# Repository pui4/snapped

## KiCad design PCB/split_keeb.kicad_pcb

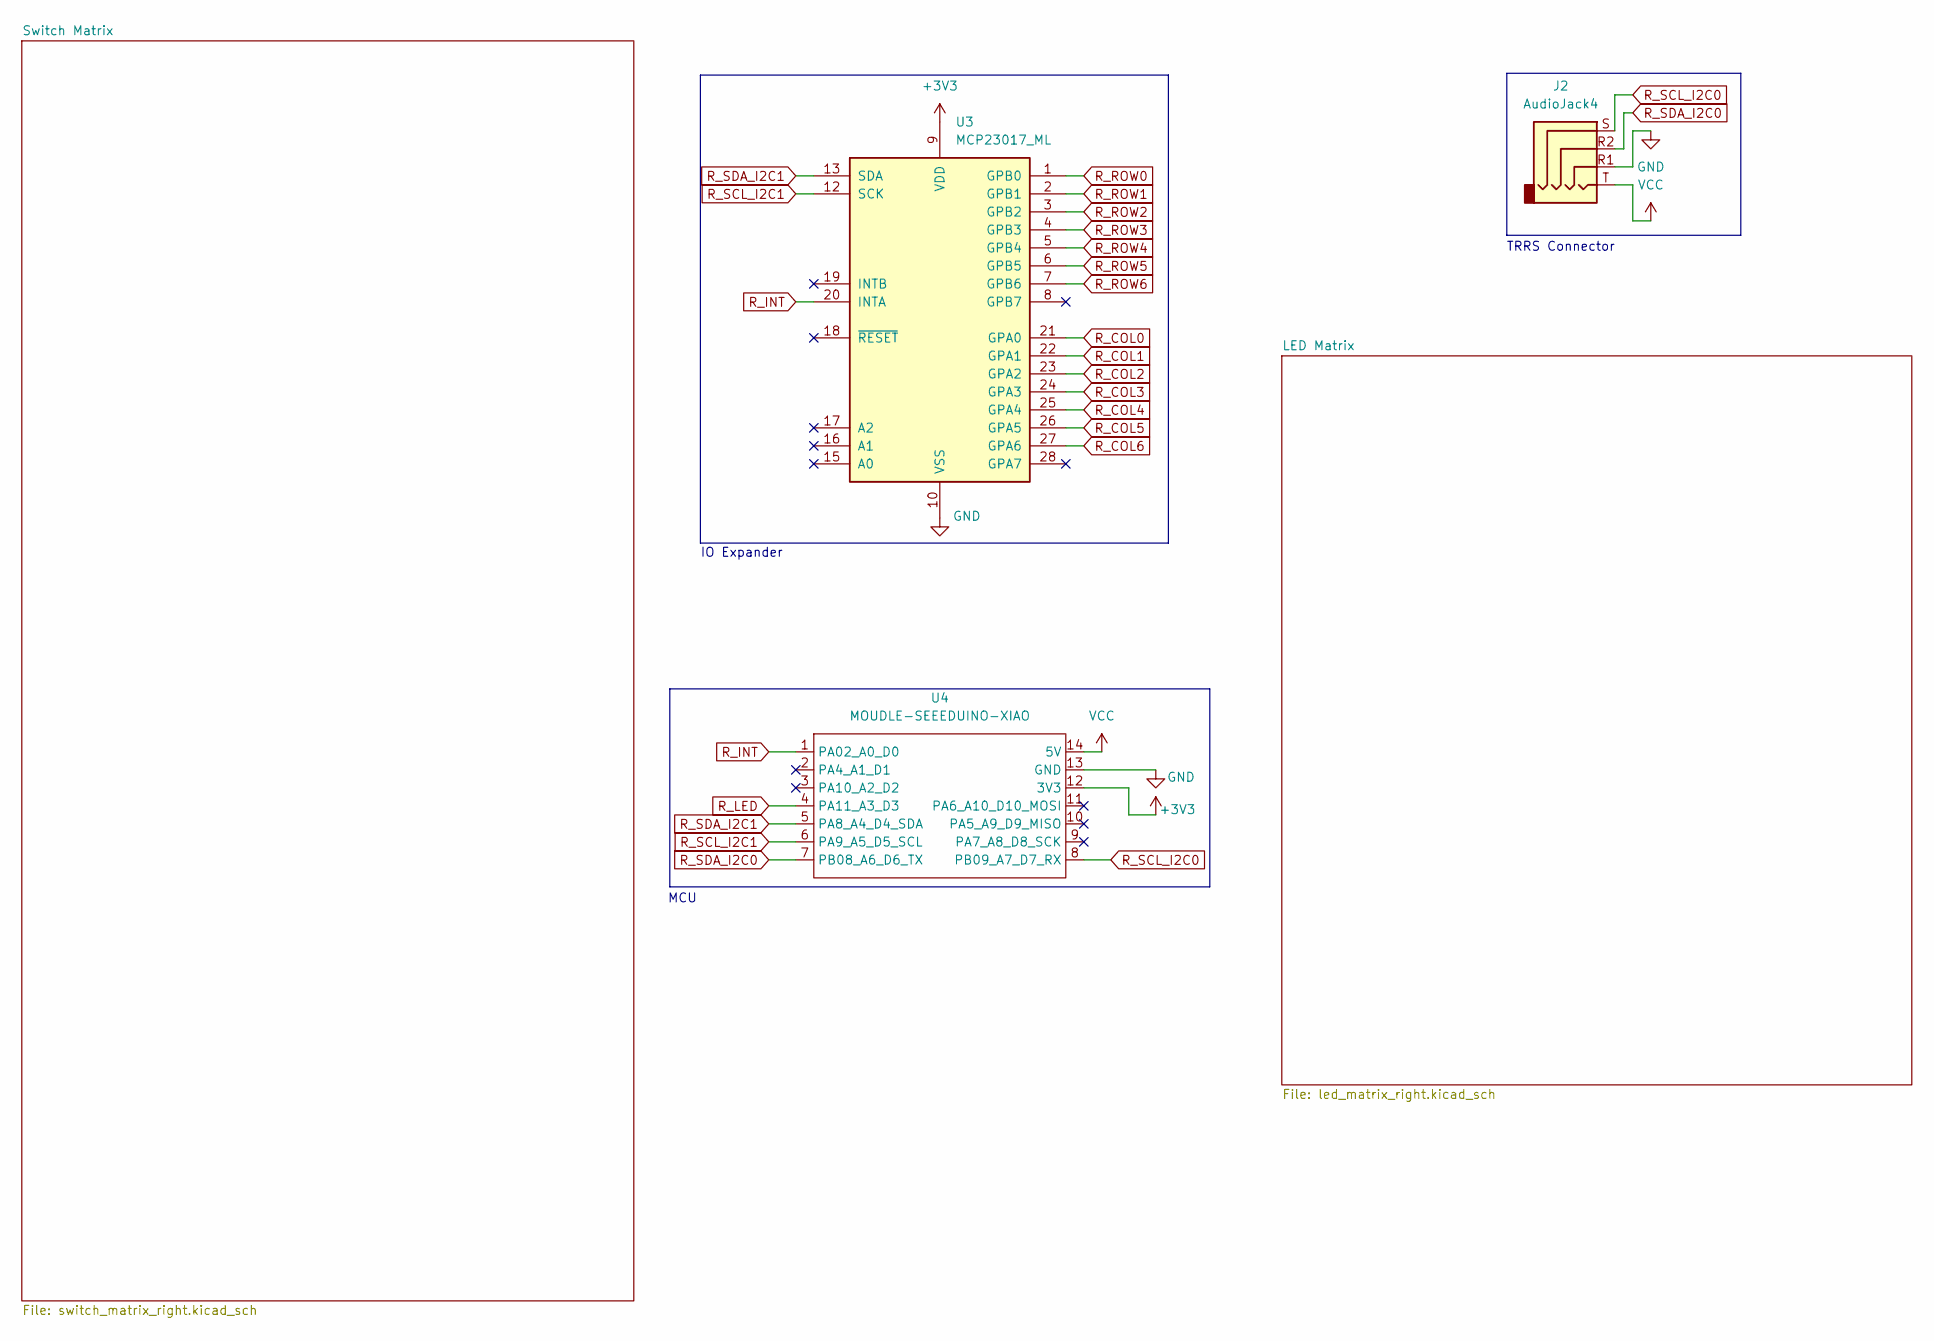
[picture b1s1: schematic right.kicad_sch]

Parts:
J2: AudioJack4; Jack_3.5mm_PJ320D_Horizontal
U3: MCP23017_ML; DIP-28_W7.62mm
U4: MOUDLE-SEEEDUINO-XIAO; XIAO-Generic-Hybrid-14P-2.54-21X17.8MM

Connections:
+3V3: U3.9 (VDD), U4.12 (3V3); also elsewhere on the board
GND: J2.R1, U3.10 (VSS), U4.13 (GND); also elsewhere on the board
R_COL0: U3.21 (GPA0); also elsewhere on the board
R_COL1: U3.22 (GPA1); also elsewhere on the board
R_COL2: U3.23 (GPA2); also elsewhere on the board
R_COL3: U3.24 (GPA3); also elsewhere on the board
R_COL4: U3.25 (GPA4); also elsewhere on the board
R_COL5: U3.26 (GPA5); also elsewhere on the board
R_COL6: U3.27 (GPA6); also elsewhere on the board
R_INT: U3.20 (INTA), U4.1 (PA02_A0_D0)
R_LED: U4.4 (PA11_A3_D3); also elsewhere on the board
R_ROW0: U3.1 (GPB0); also elsewhere on the board
R_ROW1: U3.2 (GPB1); also elsewhere on the board
R_ROW2: U3.3 (GPB2); also elsewhere on the board
R_ROW3: U3.4 (GPB3); also elsewhere on the board
R_ROW4: U3.5 (GPB4); also elsewhere on the board
R_ROW5: U3.6 (GPB5); also elsewhere on the board
R_ROW6: U3.7 (GPB6); also elsewhere on the board
R_SCL_I2C0: J2.S, U4.8 (PB09_A7_D7_RX)
R_SCL_I2C1: U3.12 (SCK), U4.6 (PA9_A5_D5_SCL)
R_SDA_I2C0: J2.R2, U4.7 (PB08_A6_D6_TX)
R_SDA_I2C1: U3.13 (SDA), U4.5 (PA8_A4_D4_SDA)
VCC: J2.T, U4.14 (5V); also elsewhere on the board

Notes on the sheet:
IO Expander
TRRS Connector
MCU

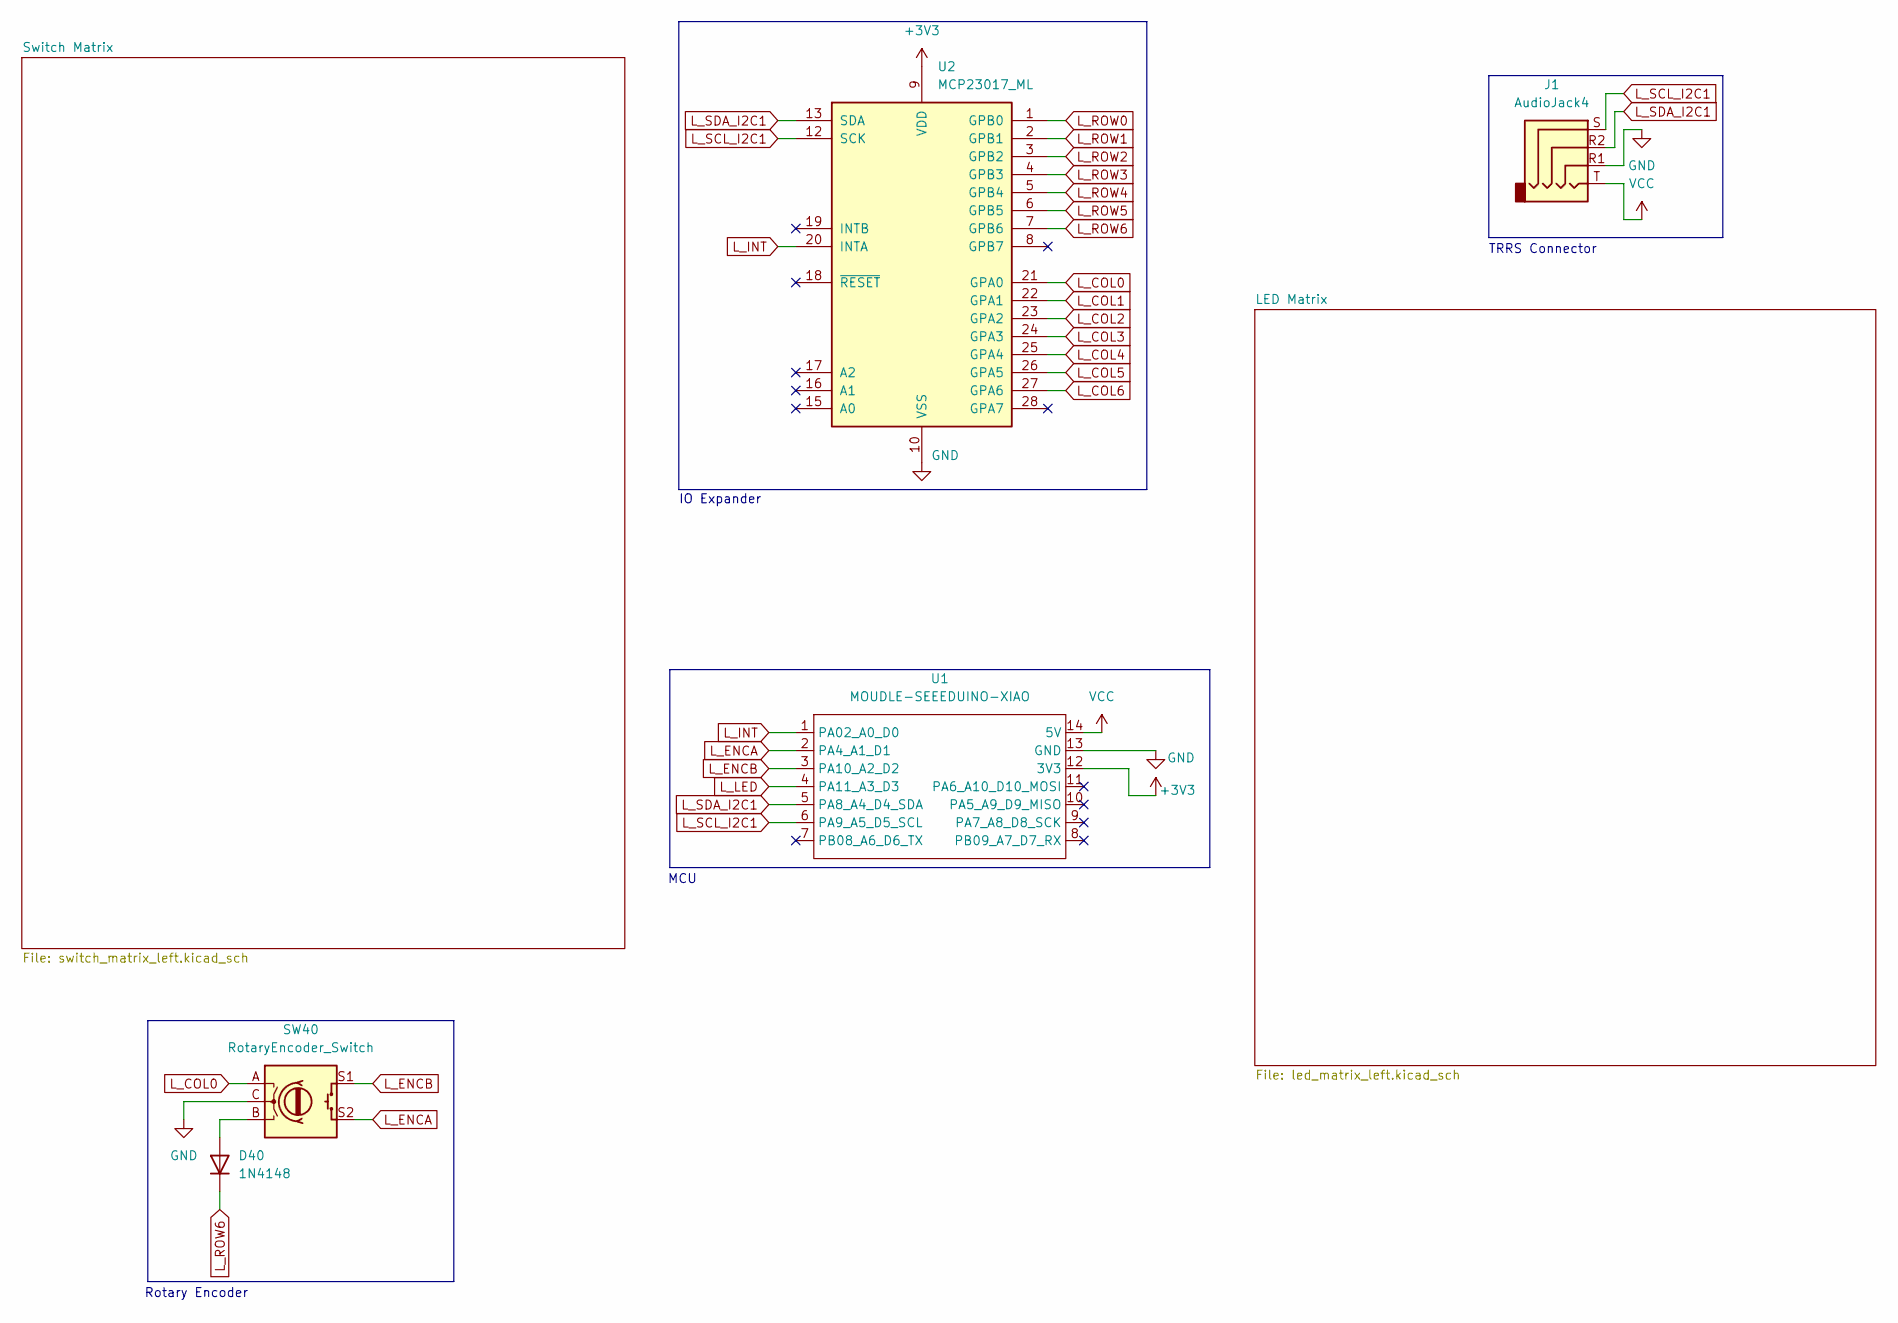
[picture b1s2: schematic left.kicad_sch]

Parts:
D40: 1N4148; D_DO-35_SOD27_P7.62mm_Horizontal
J1: AudioJack4; Jack_3.5mm_PJ320D_Horizontal
SW40: RotaryEncoder_Switch; RotaryEncoder_Alps_EC11E-Switch_Vertical_H20mm
U1: MOUDLE-SEEEDUINO-XIAO; XIAO-Generic-Hybrid-14P-2.54-21X17.8MM
U2: MCP23017_ML; DIP-28_W7.62mm

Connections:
+3V3: U1.12 (3V3), U2.9 (VDD); also elsewhere on the board
GND: J1.R1, SW40.C, U1.13 (GND), U2.10 (VSS); also elsewhere on the board
L_COL0: SW40.A, U2.21 (GPA0); also elsewhere on the board
L_COL1: U2.22 (GPA1); also elsewhere on the board
L_COL2: U2.23 (GPA2); also elsewhere on the board
L_COL3: U2.24 (GPA3); also elsewhere on the board
L_COL4: U2.25 (GPA4); also elsewhere on the board
L_COL5: U2.26 (GPA5); also elsewhere on the board
L_COL6: U2.27 (GPA6); also elsewhere on the board
L_ENCA: SW40.S2, U1.2 (PA4_A1_D1)
L_ENCB: SW40.S1, U1.3 (PA10_A2_D2)
L_INT: U1.1 (PA02_A0_D0), U2.20 (INTA)
L_LED: U1.4 (PA11_A3_D3); also elsewhere on the board
L_ROW0: U2.1 (GPB0); also elsewhere on the board
L_ROW1: U2.2 (GPB1); also elsewhere on the board
L_ROW2: U2.3 (GPB2); also elsewhere on the board
L_ROW3: U2.4 (GPB3); also elsewhere on the board
L_ROW4: U2.5 (GPB4); also elsewhere on the board
L_ROW5: U2.6 (GPB5); also elsewhere on the board
L_ROW6: D40.1 (K), U2.7 (GPB6); also elsewhere on the board
L_SCL_I2C1: J1.S, U1.6 (PA9_A5_D5_SCL), U2.12 (SCK)
L_SDA_I2C1: J1.R2, U1.5 (PA8_A4_D4_SDA), U2.13 (SDA)
unnamed: D40.2 (A), SW40.B
VCC: J1.T, U1.14 (5V); also elsewhere on the board

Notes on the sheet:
TRRS Connector
MCU
IO Expander
Rotary Encoder

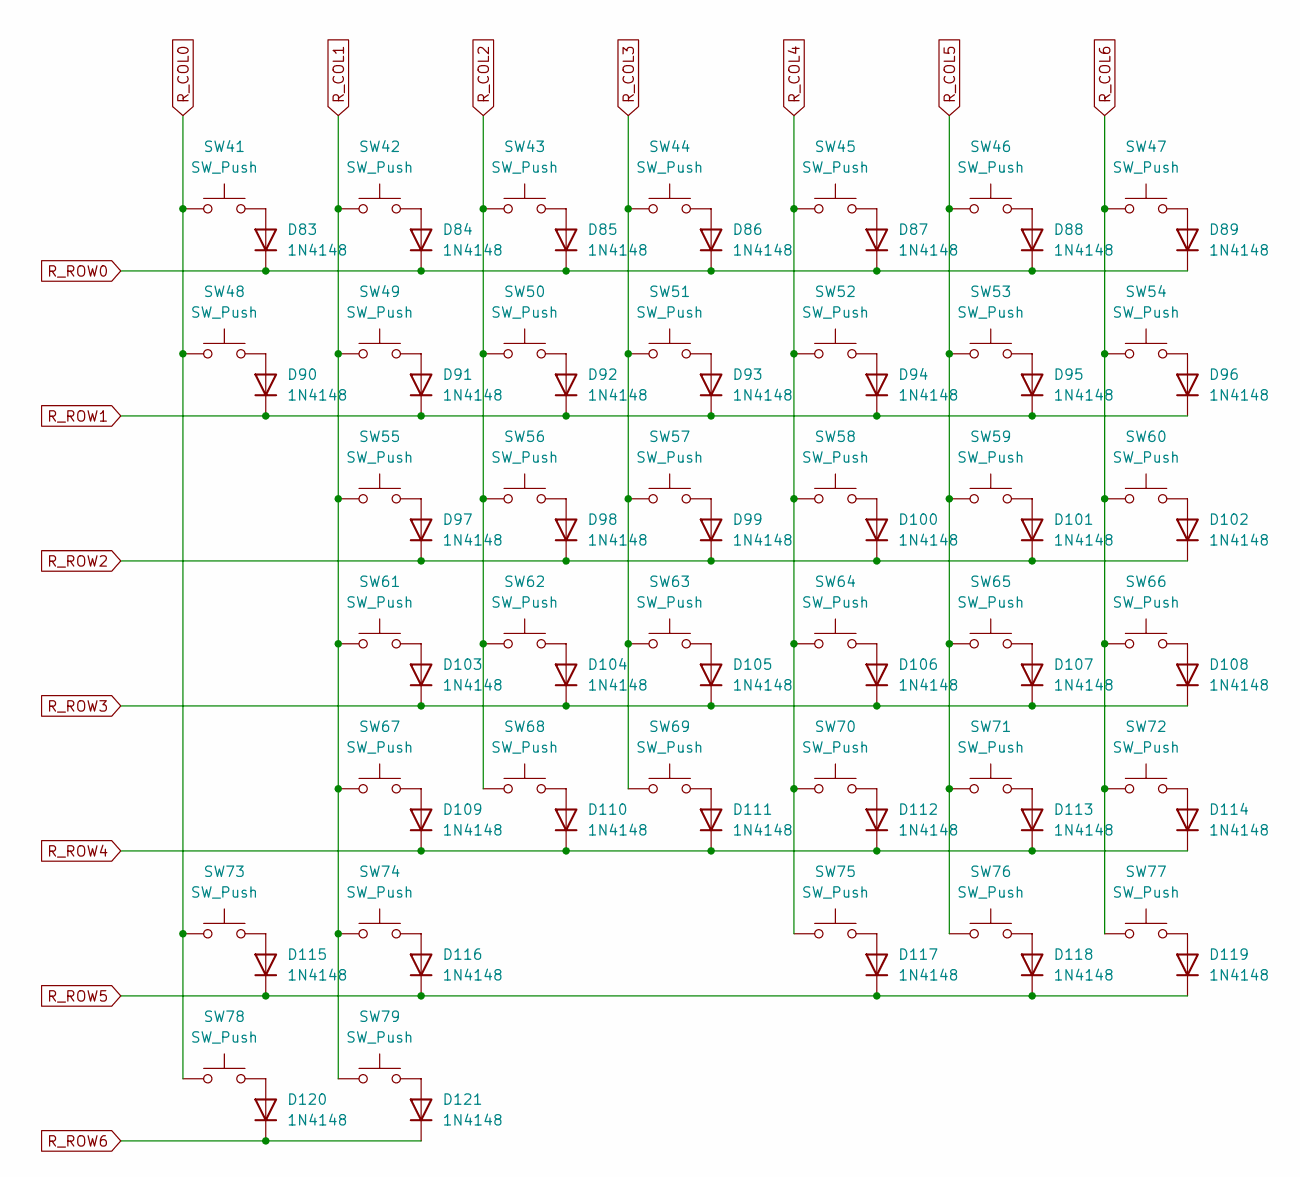
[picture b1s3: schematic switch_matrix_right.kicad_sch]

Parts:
D83, D84, D85, D86, D87, D88, D89, D90, D91, D92, D93, D94, D95, D96, D97, D98, D99, D100, D101, D102, D103, D104, D105, D106, D107, D108, D109, D110, D111, D112, D113, D114, D115, D116, D117, D118, D119, D120, D121: 1N4148; D_DO-35_SOD27_P7.62mm_Horizontal
SW41, SW42, SW43, SW44, SW45, SW46, SW47, SW48, SW49, SW50, SW51, SW52, SW53, SW54, SW55, SW56, SW57, SW58, SW59, SW61, SW62, SW63, SW64, SW65, SW67, SW68, SW69, SW70, SW71, SW74, SW75, SW76, SW79: SW_Push; SW_KS33_HS_KS-2P02B01-02_HS_1u
SW60, SW66, SW72, SW77: SW_Push; SW_KS33_HS_KS-2P02B01-02_1.25u
SW73, SW78: SW_Push; SW_KS33_HS_KS-2P02B01-02_1.75u

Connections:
unnamed: D83.2 (A), SW41.2
unnamed: D84.2 (A), SW42.2
unnamed: D85.2 (A), SW43.2
unnamed: D86.2 (A), SW44.2
unnamed: D87.2 (A), SW45.2
unnamed: D88.2 (A), SW46.2
unnamed: D89.2 (A), SW47.2
unnamed: D90.2 (A), SW48.2
unnamed: D91.2 (A), SW49.2
unnamed: D92.2 (A), SW50.2
unnamed: D93.2 (A), SW51.2
unnamed: D94.2 (A), SW52.2
unnamed: D95.2 (A), SW53.2
unnamed: D96.2 (A), SW54.2
unnamed: D97.2 (A), SW55.2
unnamed: D98.2 (A), SW56.2
unnamed: D99.2 (A), SW57.2
unnamed: D100.2 (A), SW58.2
unnamed: D101.2 (A), SW59.2
unnamed: D102.2 (A), SW60.2
unnamed: D103.2 (A), SW61.2
unnamed: D104.2 (A), SW62.2
unnamed: D105.2 (A), SW63.2
unnamed: D106.2 (A), SW64.2
unnamed: D107.2 (A), SW65.2
unnamed: D108.2 (A), SW66.2
unnamed: D109.2 (A), SW67.2
unnamed: D110.2 (A), SW68.2
unnamed: D111.2 (A), SW69.2
unnamed: D112.2 (A), SW70.2
unnamed: D113.2 (A), SW71.2
unnamed: D114.2 (A), SW72.2
unnamed: D115.2 (A), SW73.2
unnamed: D116.2 (A), SW74.2
unnamed: D117.2 (A), SW75.2
unnamed: D118.2 (A), SW76.2
unnamed: D119.2 (A), SW77.2
unnamed: D120.2 (A), SW78.2
unnamed: D121.2 (A), SW79.2
R_COL0: SW41.1, SW48.1, SW73.1, SW78.1; also elsewhere on the board
R_COL1: SW42.1, SW49.1, SW55.1, SW61.1, SW67.1, SW74.1, SW79.1; also elsewhere on the board
R_COL2: SW43.1, SW50.1, SW56.1, SW62.1, SW68.1; also elsewhere on the board
R_COL3: SW44.1, SW51.1, SW57.1, SW63.1, SW69.1; also elsewhere on the board
R_COL4: SW45.1, SW52.1, SW58.1, SW64.1, SW70.1, SW75.1; also elsewhere on the board
R_COL5: SW46.1, SW53.1, SW59.1, SW65.1, SW71.1, SW76.1; also elsewhere on the board
R_COL6: SW47.1, SW54.1, SW60.1, SW66.1, SW72.1, SW77.1; also elsewhere on the board
R_ROW0: D83.1 (K), D84.1 (K), D85.1 (K), D86.1 (K), D87.1 (K), D88.1 (K), D89.1 (K); also elsewhere on the board
R_ROW1: D90.1 (K), D91.1 (K), D92.1 (K), D93.1 (K), D94.1 (K), D95.1 (K), D96.1 (K); also elsewhere on the board
R_ROW2: D97.1 (K), D98.1 (K), D99.1 (K), D100.1 (K), D101.1 (K), D102.1 (K); also elsewhere on the board
R_ROW3: D103.1 (K), D104.1 (K), D105.1 (K), D106.1 (K), D107.1 (K), D108.1 (K); also elsewhere on the board
R_ROW4: D109.1 (K), D110.1 (K), D111.1 (K), D112.1 (K), D113.1 (K), D114.1 (K); also elsewhere on the board
R_ROW5: D115.1 (K), D116.1 (K), D117.1 (K), D118.1 (K), D119.1 (K); also elsewhere on the board
R_ROW6: D120.1 (K), D121.1 (K); also elsewhere on the board

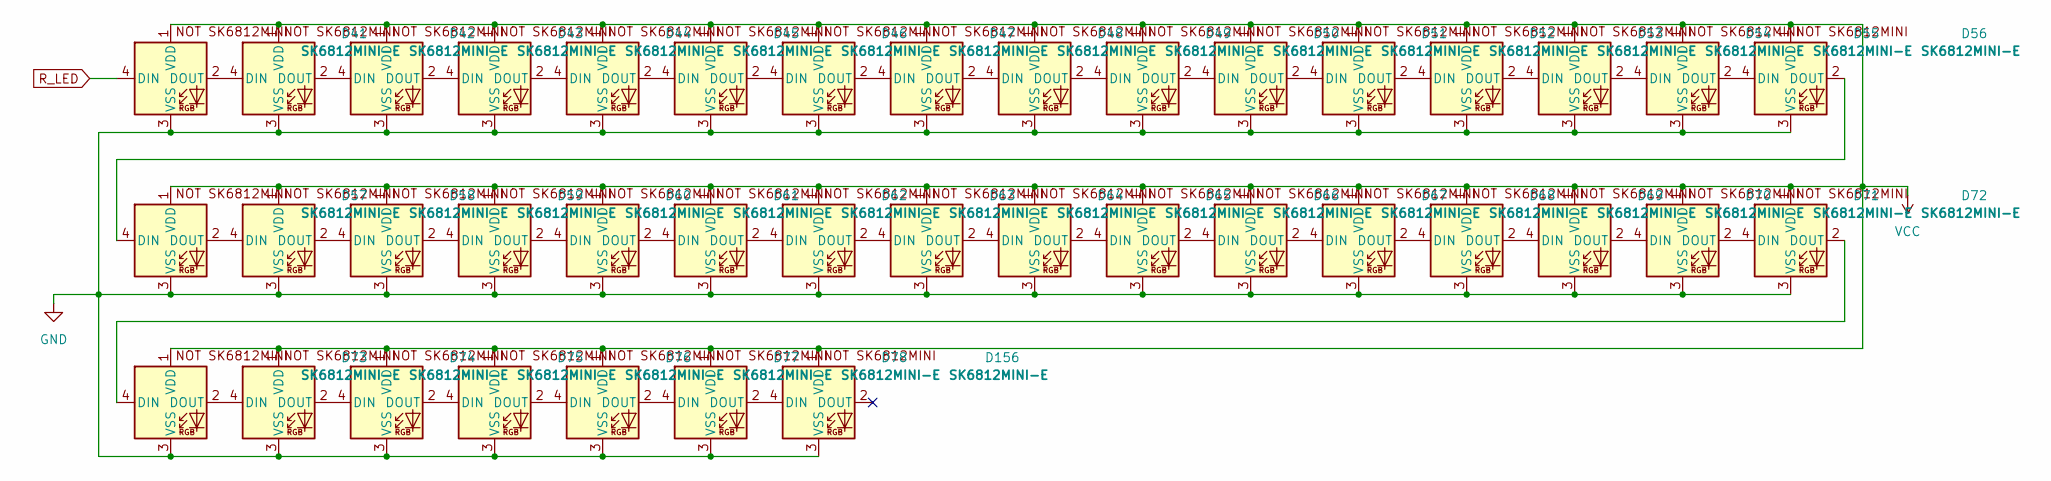
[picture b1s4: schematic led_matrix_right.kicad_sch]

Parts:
D41, D42, D43, D44, D45, D46, D47, D48, D49, D50, D51, D52, D53, D54, D55, D56, D57, D58, D59, D60, D61, D62, D63, D64, D65, D66, D67, D68, D69, D70, D71, D72, D73, D74, D75, D76, D77, D78, D156: SK6812MINI-E; SK6812MINI-E_fixed

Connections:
GND: D41.3 (VSS), D42.3 (VSS), D43.3 (VSS), D44.3 (VSS), D45.3 (VSS), D46.3 (VSS), D47.3 (VSS), D48.3 (VSS), D49.3 (VSS), D50.3 (VSS), D51.3 (VSS), D52.3 (VSS), D53.3 (VSS), D54.3 (VSS), D55.3 (VSS), D56.3 (VSS), D57.3 (VSS), D58.3 (VSS), D59.3 (VSS), D60.3 (VSS), D61.3 (VSS), D62.3 (VSS), D63.3 (VSS), D64.3 (VSS), D65.3 (VSS), D66.3 (VSS), D67.3 (VSS), D68.3 (VSS), D69.3 (VSS), D70.3 (VSS), D71.3 (VSS), D72.3 (VSS), D73.3 (VSS), D74.3 (VSS), D75.3 (VSS), D76.3 (VSS), D77.3 (VSS), D78.3 (VSS), D156.3 (VSS); also elsewhere on the board
unnamed: D41.2 (DOUT), D42.4 (DIN)
unnamed: D42.2 (DOUT), D43.4 (DIN)
unnamed: D43.2 (DOUT), D44.4 (DIN)
unnamed: D44.2 (DOUT), D45.4 (DIN)
unnamed: D45.2 (DOUT), D46.4 (DIN)
unnamed: D46.2 (DOUT), D47.4 (DIN)
unnamed: D47.2 (DOUT), D48.4 (DIN)
unnamed: D48.2 (DOUT), D49.4 (DIN)
unnamed: D49.2 (DOUT), D50.4 (DIN)
unnamed: D50.2 (DOUT), D51.4 (DIN)
unnamed: D51.2 (DOUT), D52.4 (DIN)
unnamed: D52.2 (DOUT), D53.4 (DIN)
unnamed: D53.2 (DOUT), D54.4 (DIN)
unnamed: D54.2 (DOUT), D55.4 (DIN)
unnamed: D55.2 (DOUT), D56.4 (DIN)
unnamed: D56.2 (DOUT), D57.4 (DIN)
unnamed: D57.2 (DOUT), D58.4 (DIN)
unnamed: D58.2 (DOUT), D59.4 (DIN)
unnamed: D59.2 (DOUT), D60.4 (DIN)
unnamed: D60.2 (DOUT), D61.4 (DIN)
unnamed: D61.2 (DOUT), D62.4 (DIN)
unnamed: D62.2 (DOUT), D63.4 (DIN)
unnamed: D63.2 (DOUT), D64.4 (DIN)
unnamed: D64.2 (DOUT), D65.4 (DIN)
unnamed: D65.2 (DOUT), D66.4 (DIN)
unnamed: D66.2 (DOUT), D67.4 (DIN)
unnamed: D67.2 (DOUT), D68.4 (DIN)
unnamed: D68.2 (DOUT), D69.4 (DIN)
unnamed: D69.2 (DOUT), D70.4 (DIN)
unnamed: D70.2 (DOUT), D71.4 (DIN)
unnamed: D71.2 (DOUT), D72.4 (DIN)
unnamed: D72.2 (DOUT), D73.4 (DIN)
unnamed: D73.2 (DOUT), D74.4 (DIN)
unnamed: D74.2 (DOUT), D75.4 (DIN)
unnamed: D75.2 (DOUT), D76.4 (DIN)
unnamed: D76.2 (DOUT), D77.4 (DIN)
unnamed: D77.2 (DOUT), D78.4 (DIN)
unnamed: D78.2 (DOUT), D156.4 (DIN)
R_LED: D41.4 (DIN); also elsewhere on the board
VCC: D41.1 (VDD), D42.1 (VDD), D43.1 (VDD), D44.1 (VDD), D45.1 (VDD), D46.1 (VDD), D47.1 (VDD), D48.1 (VDD), D49.1 (VDD), D50.1 (VDD), D51.1 (VDD), D52.1 (VDD), D53.1 (VDD), D54.1 (VDD), D55.1 (VDD), D56.1 (VDD), D57.1 (VDD), D58.1 (VDD), D59.1 (VDD), D60.1 (VDD), D61.1 (VDD), D62.1 (VDD), D63.1 (VDD), D64.1 (VDD), D65.1 (VDD), D66.1 (VDD), D67.1 (VDD), D68.1 (VDD), D69.1 (VDD), D70.1 (VDD), D71.1 (VDD), D72.1 (VDD), D73.1 (VDD), D74.1 (VDD), D75.1 (VDD), D76.1 (VDD), D77.1 (VDD), D78.1 (VDD), D156.1 (VDD); also elsewhere on the board

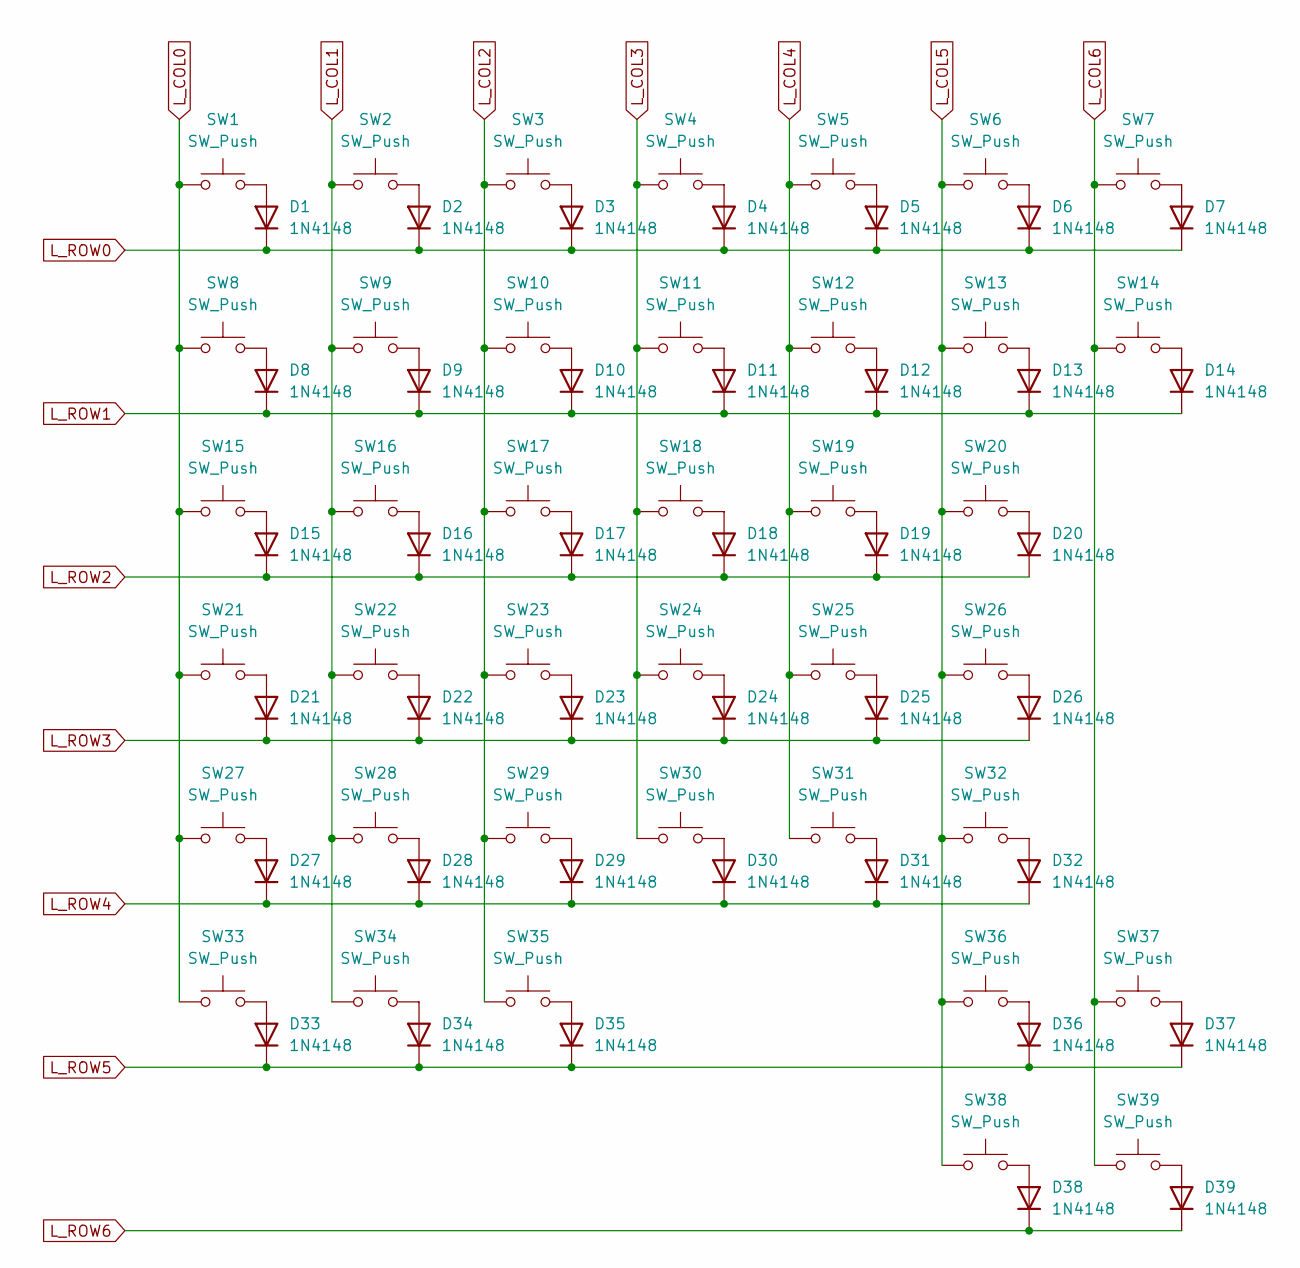
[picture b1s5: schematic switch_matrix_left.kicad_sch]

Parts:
D1, D2, D3, D4, D5, D6, D7, D8, D9, D10, D11, D12, D13, D14, D15, D16, D17, D18, D19, D20, D21, D22, D23, D24, D25, D26, D27, D28, D29, D30, D31, D32, D33, D34, D35, D36, D37, D38, D39: 1N4148; D_DO-35_SOD27_P7.62mm_Horizontal
SW1, SW2, SW3, SW4, SW5, SW6, SW7, SW8, SW9, SW10, SW11, SW12, SW13, SW14, SW16, SW17, SW18, SW19, SW20, SW22, SW23, SW24, SW25, SW26, SW28, SW29, SW30, SW31, SW32, SW34, SW35, SW37, SW39: SW_Push; SW_KS33_HS_KS-2P02B01-02_HS_1u
SW15, SW21, SW27, SW33: SW_Push; SW_KS33_HS_KS-2P02B01-02_1.25u
SW36, SW38: SW_Push; SW_KS33_HS_KS-2P02B01-02_1.75u

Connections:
L_COL0: SW1.1, SW8.1, SW15.1, SW21.1, SW27.1, SW33.1; also elsewhere on the board
L_COL1: SW2.1, SW9.1, SW16.1, SW22.1, SW28.1, SW34.1; also elsewhere on the board
L_COL2: SW3.1, SW10.1, SW17.1, SW23.1, SW29.1, SW35.1; also elsewhere on the board
L_COL3: SW4.1, SW11.1, SW18.1, SW24.1, SW30.1; also elsewhere on the board
L_COL4: SW5.1, SW12.1, SW19.1, SW25.1, SW31.1; also elsewhere on the board
L_COL5: SW6.1, SW13.1, SW20.1, SW26.1, SW32.1, SW36.1, SW38.1; also elsewhere on the board
L_COL6: SW7.1, SW14.1, SW37.1, SW39.1; also elsewhere on the board
L_ROW0: D1.1 (K), D2.1 (K), D3.1 (K), D4.1 (K), D5.1 (K), D6.1 (K), D7.1 (K); also elsewhere on the board
L_ROW1: D8.1 (K), D9.1 (K), D10.1 (K), D11.1 (K), D12.1 (K), D13.1 (K), D14.1 (K); also elsewhere on the board
L_ROW2: D15.1 (K), D16.1 (K), D17.1 (K), D18.1 (K), D19.1 (K), D20.1 (K); also elsewhere on the board
L_ROW3: D21.1 (K), D22.1 (K), D23.1 (K), D24.1 (K), D25.1 (K), D26.1 (K); also elsewhere on the board
L_ROW4: D27.1 (K), D28.1 (K), D29.1 (K), D30.1 (K), D31.1 (K), D32.1 (K); also elsewhere on the board
L_ROW5: D33.1 (K), D34.1 (K), D35.1 (K), D36.1 (K), D37.1 (K); also elsewhere on the board
L_ROW6: D38.1 (K), D39.1 (K); also elsewhere on the board
unnamed: D1.2 (A), SW1.2
unnamed: D2.2 (A), SW2.2
unnamed: D3.2 (A), SW3.2
unnamed: D4.2 (A), SW4.2
unnamed: D5.2 (A), SW5.2
unnamed: D6.2 (A), SW6.2
unnamed: D7.2 (A), SW7.2
unnamed: D8.2 (A), SW8.2
unnamed: D9.2 (A), SW9.2
unnamed: D10.2 (A), SW10.2
unnamed: D11.2 (A), SW11.2
unnamed: D12.2 (A), SW12.2
unnamed: D13.2 (A), SW13.2
unnamed: D14.2 (A), SW14.2
unnamed: D15.2 (A), SW15.2
unnamed: D16.2 (A), SW16.2
unnamed: D17.2 (A), SW17.2
unnamed: D18.2 (A), SW18.2
unnamed: D19.2 (A), SW19.2
unnamed: D20.2 (A), SW20.2
unnamed: D21.2 (A), SW21.2
unnamed: D22.2 (A), SW22.2
unnamed: D23.2 (A), SW23.2
unnamed: D24.2 (A), SW24.2
unnamed: D25.2 (A), SW25.2
unnamed: D26.2 (A), SW26.2
unnamed: D27.2 (A), SW27.2
unnamed: D28.2 (A), SW28.2
unnamed: D29.2 (A), SW29.2
unnamed: D30.2 (A), SW30.2
unnamed: D31.2 (A), SW31.2
unnamed: D32.2 (A), SW32.2
unnamed: D33.2 (A), SW33.2
unnamed: D34.2 (A), SW34.2
unnamed: D35.2 (A), SW35.2
unnamed: D36.2 (A), SW36.2
unnamed: D37.2 (A), SW37.2
unnamed: D38.2 (A), SW38.2
unnamed: D39.2 (A), SW39.2

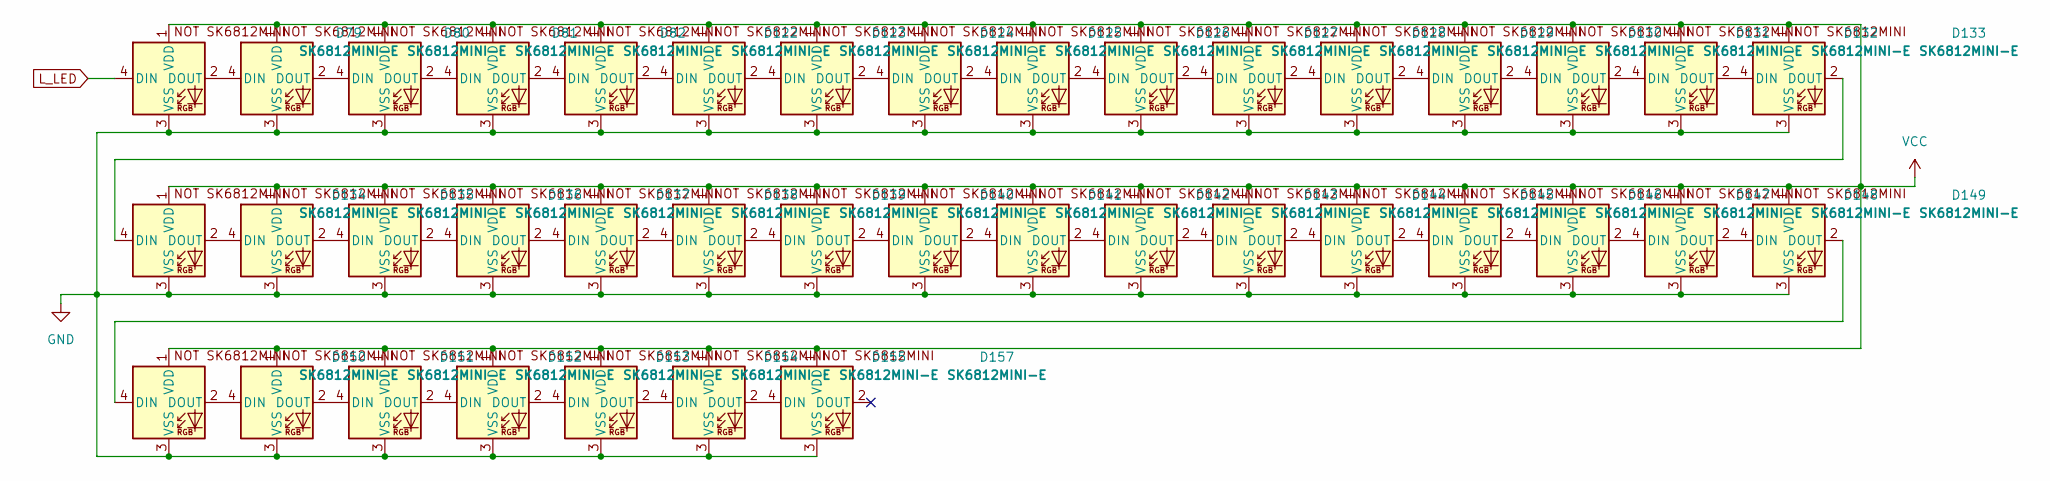
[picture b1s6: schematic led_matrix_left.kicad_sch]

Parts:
D79, D80, D81, D82, D122, D123, D124, D125, D126, D127, D128, D129, D130, D131, D132, D133, D134, D135, D136, D137, D138, D139, D140, D141, D142, D143, D144, D145, D146, D147, D148, D149, D150, D151, D152, D153, D154, D155, D157: SK6812MINI-E; SK6812MINI-E_fixed

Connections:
GND: D79.3 (VSS), D80.3 (VSS), D81.3 (VSS), D82.3 (VSS), D122.3 (VSS), D123.3 (VSS), D124.3 (VSS), D125.3 (VSS), D126.3 (VSS), D127.3 (VSS), D128.3 (VSS), D129.3 (VSS), D130.3 (VSS), D131.3 (VSS), D132.3 (VSS), D133.3 (VSS), D134.3 (VSS), D135.3 (VSS), D136.3 (VSS), D137.3 (VSS), D138.3 (VSS), D139.3 (VSS), D140.3 (VSS), D141.3 (VSS), D142.3 (VSS), D143.3 (VSS), D144.3 (VSS), D145.3 (VSS), D146.3 (VSS), D147.3 (VSS), D148.3 (VSS), D149.3 (VSS), D150.3 (VSS), D151.3 (VSS), D152.3 (VSS), D153.3 (VSS), D154.3 (VSS), D155.3 (VSS), D157.3 (VSS); also elsewhere on the board
L_LED: D79.4 (DIN); also elsewhere on the board
unnamed: D79.2 (DOUT), D80.4 (DIN)
unnamed: D80.2 (DOUT), D81.4 (DIN)
unnamed: D81.2 (DOUT), D82.4 (DIN)
unnamed: D82.2 (DOUT), D122.4 (DIN)
unnamed: D122.2 (DOUT), D123.4 (DIN)
unnamed: D123.2 (DOUT), D124.4 (DIN)
unnamed: D124.2 (DOUT), D125.4 (DIN)
unnamed: D125.2 (DOUT), D126.4 (DIN)
unnamed: D126.2 (DOUT), D127.4 (DIN)
unnamed: D127.2 (DOUT), D128.4 (DIN)
unnamed: D128.2 (DOUT), D129.4 (DIN)
unnamed: D129.2 (DOUT), D130.4 (DIN)
unnamed: D130.2 (DOUT), D131.4 (DIN)
unnamed: D131.2 (DOUT), D132.4 (DIN)
unnamed: D132.2 (DOUT), D133.4 (DIN)
unnamed: D133.2 (DOUT), D134.4 (DIN)
unnamed: D134.2 (DOUT), D135.4 (DIN)
unnamed: D135.2 (DOUT), D136.4 (DIN)
unnamed: D136.2 (DOUT), D137.4 (DIN)
unnamed: D137.2 (DOUT), D138.4 (DIN)
unnamed: D138.2 (DOUT), D139.4 (DIN)
unnamed: D139.2 (DOUT), D140.4 (DIN)
unnamed: D140.2 (DOUT), D141.4 (DIN)
unnamed: D141.2 (DOUT), D142.4 (DIN)
unnamed: D142.2 (DOUT), D143.4 (DIN)
unnamed: D143.2 (DOUT), D144.4 (DIN)
unnamed: D144.2 (DOUT), D145.4 (DIN)
unnamed: D145.2 (DOUT), D146.4 (DIN)
unnamed: D146.2 (DOUT), D147.4 (DIN)
unnamed: D147.2 (DOUT), D148.4 (DIN)
unnamed: D148.2 (DOUT), D149.4 (DIN)
unnamed: D149.2 (DOUT), D150.4 (DIN)
unnamed: D150.2 (DOUT), D151.4 (DIN)
unnamed: D151.2 (DOUT), D152.4 (DIN)
unnamed: D152.2 (DOUT), D153.4 (DIN)
unnamed: D153.2 (DOUT), D154.4 (DIN)
unnamed: D154.2 (DOUT), D155.4 (DIN)
unnamed: D155.2 (DOUT), D157.4 (DIN)
VCC: D79.1 (VDD), D80.1 (VDD), D81.1 (VDD), D82.1 (VDD), D122.1 (VDD), D123.1 (VDD), D124.1 (VDD), D125.1 (VDD), D126.1 (VDD), D127.1 (VDD), D128.1 (VDD), D129.1 (VDD), D130.1 (VDD), D131.1 (VDD), D132.1 (VDD), D133.1 (VDD), D134.1 (VDD), D135.1 (VDD), D136.1 (VDD), D137.1 (VDD), D138.1 (VDD), D139.1 (VDD), D140.1 (VDD), D141.1 (VDD), D142.1 (VDD), D143.1 (VDD), D144.1 (VDD), D145.1 (VDD), D146.1 (VDD), D147.1 (VDD), D148.1 (VDD), D149.1 (VDD), D150.1 (VDD), D151.1 (VDD), D152.1 (VDD), D153.1 (VDD), D154.1 (VDD), D155.1 (VDD), D157.1 (VDD); also elsewhere on the board

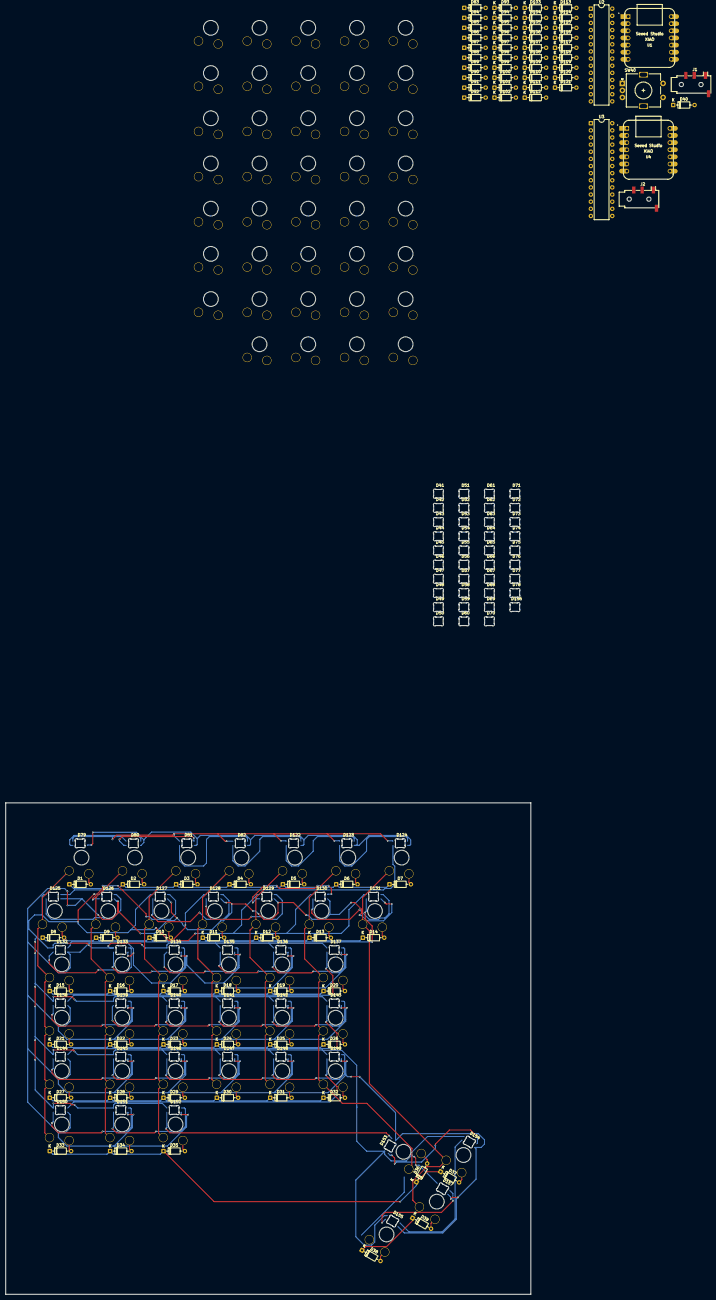
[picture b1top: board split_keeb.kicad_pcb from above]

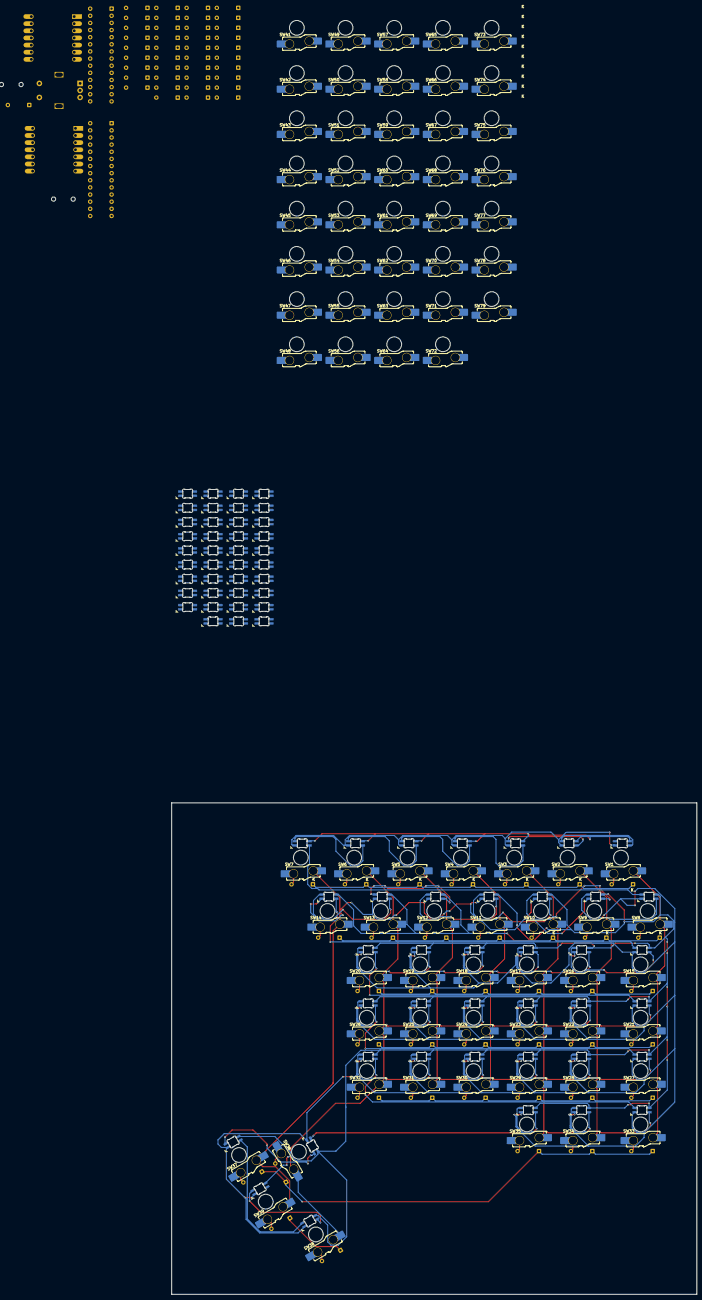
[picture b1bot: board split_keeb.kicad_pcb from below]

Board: 2 copper layers, 242 parts (78 on the bottom side), 198 nets.

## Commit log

2026-02-19 did the schematic (hopefully)
2026-02-19 added bom
2026-02-19 updated schematic
2026-02-19 routed the switches and diodes
2026-02-20 redid the leds
2026-02-20 "finished" right side
2026-02-23 wired up leds and matrix for left
